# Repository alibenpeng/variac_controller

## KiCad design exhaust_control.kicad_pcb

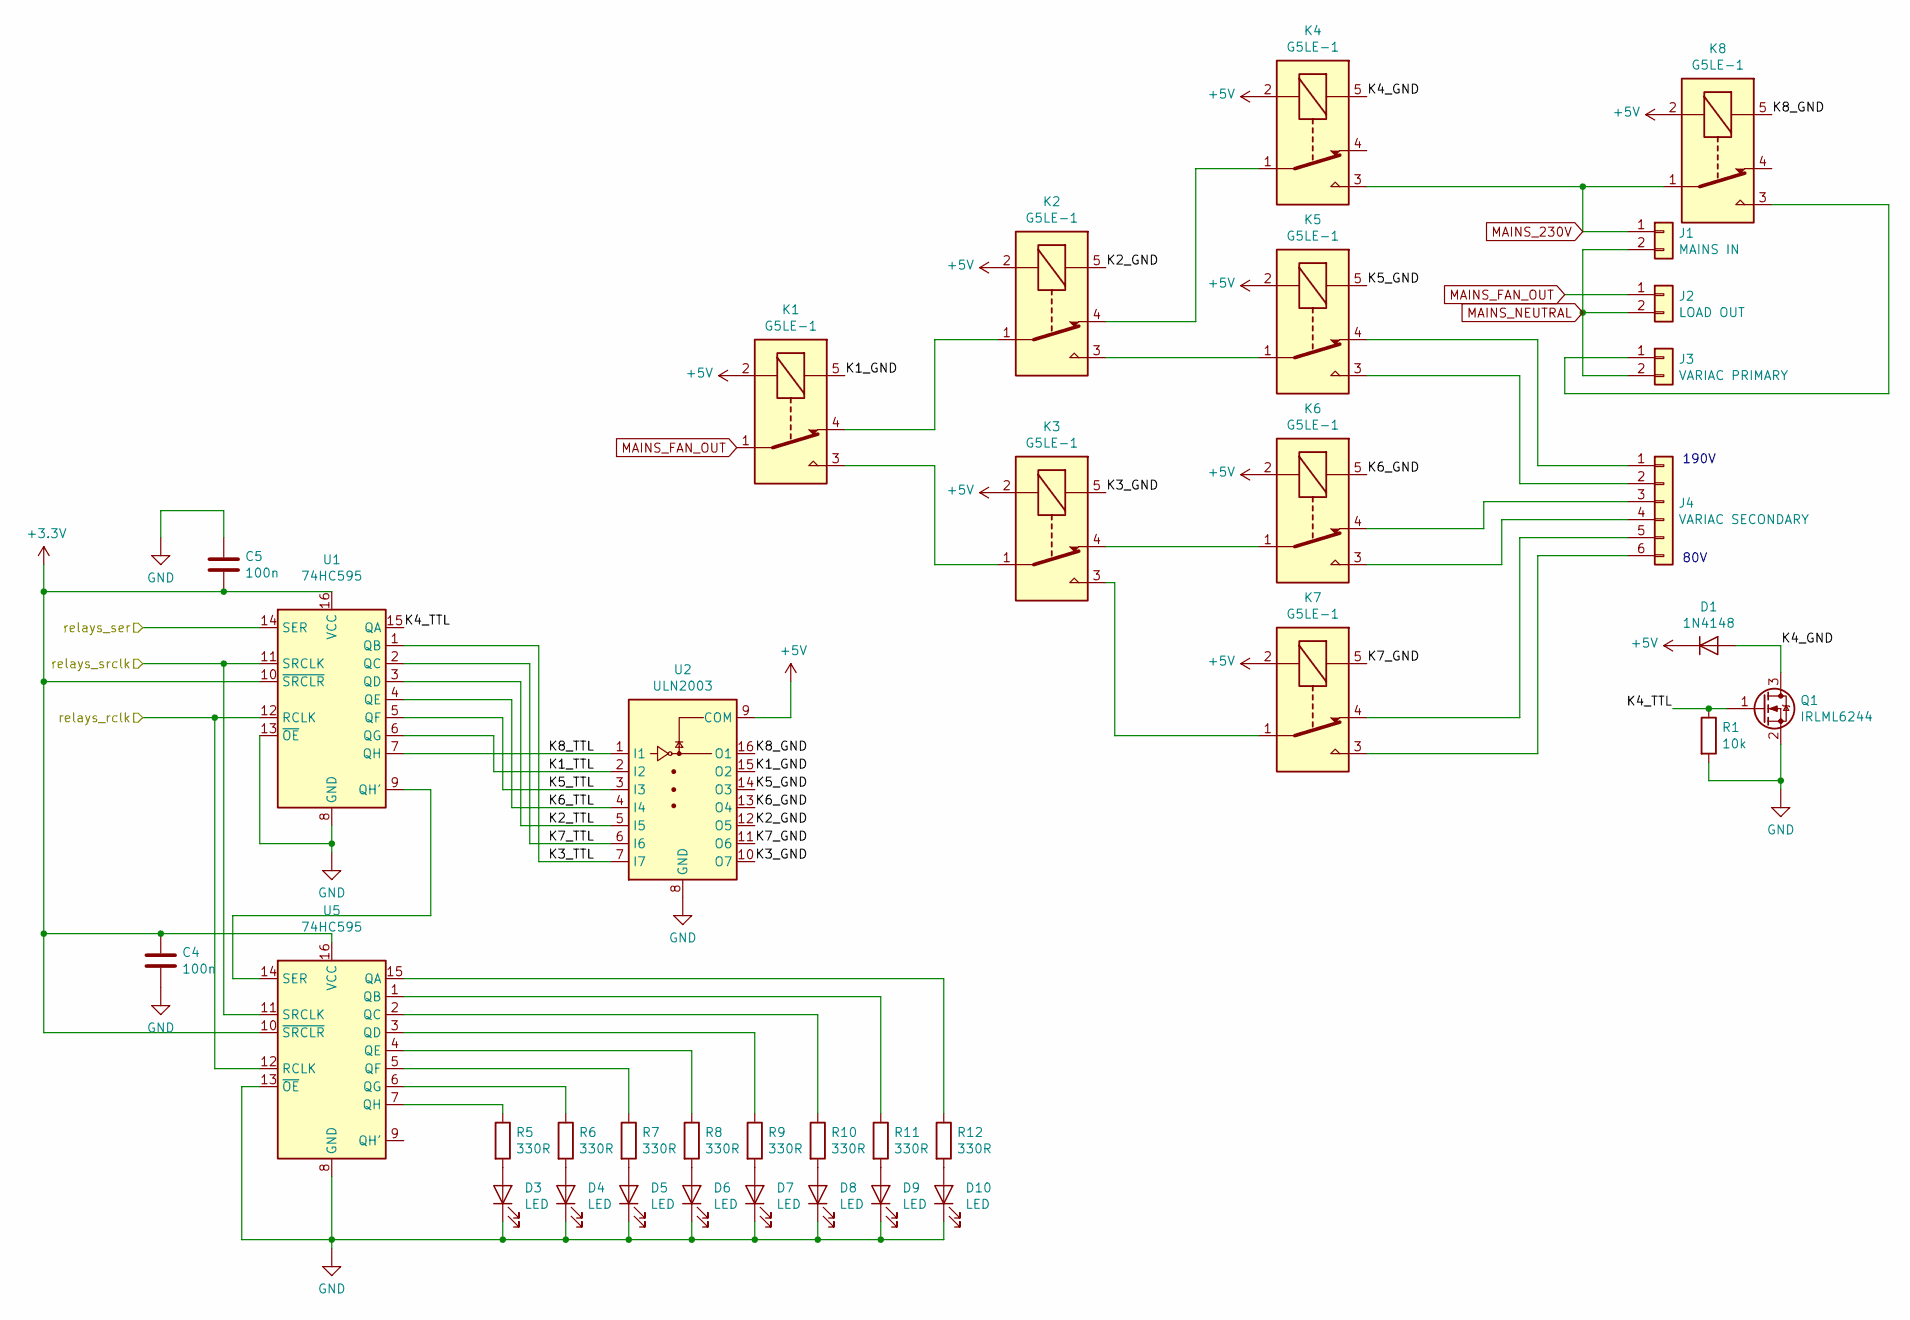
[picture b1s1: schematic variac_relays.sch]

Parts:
C4, C5: 100n; C_0402
D1: 1N4148; D_SOD-323
D3, D4, D5, D6, D7, D8, D9, D10: LED; LED-0603
J1: MAINS IN; TerminalBlock_bornier-2_P5.08mm
J2: LOAD OUT; TerminalBlock_bornier-2_P5.08mm
J3: VARIAC PRIMARY; TerminalBlock_bornier-2_P5.08mm
J4: VARIAC SECONDARY; TerminalBlock_bornier-6_P5.08mm
K1, K2, K3, K4, K5, K6, K7, K8: G5LE-1; Relay_SPDT_OMRON-G5LE-1
Q1: IRLML6244; SOT-23
R1: 10k; R_0603
R5, R6, R7, R8, R9, R10, R11, R12: 330R; R_0603
U1, U5: 74HC595; SOIC-16_3.9x9.9mm_Pitch1.27mm
U2: ULN2003; SOIC-16_3.9x9.9mm_Pitch1.27mm

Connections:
+5V: D1.1 (K), K1.2, K2.2, K3.2, K4.2, K5.2, K6.2, K7.2, K8.2, U2.9 (COM); also elsewhere on the board
/Autotransformer Relays/K1_GND: K1.5, U2.15 (O2)
/Autotransformer Relays/K1_TTL: U1.6 (QG), U2.2 (I2)
/Autotransformer Relays/K2_GND: K2.5, U2.12 (O5)
/Autotransformer Relays/K2_TTL: U1.3 (QD), U2.5 (I5)
/Autotransformer Relays/K3_GND: K3.5, U2.10 (O7)
/Autotransformer Relays/K3_TTL: U1.1 (QB), U2.7 (I7)
/Autotransformer Relays/K4_GND: D1.2 (A), K4.5, Q1.3 (D)
/Autotransformer Relays/K4_TTL: Q1.1 (G), R1.1, U1.15 (QA)
/Autotransformer Relays/K5_GND: K5.5, U2.14 (O3)
/Autotransformer Relays/K5_TTL: U1.5 (QF), U2.3 (I3)
/Autotransformer Relays/K6_GND: K6.5, U2.13 (O4)
/Autotransformer Relays/K6_TTL: U1.4 (QE), U2.4 (I4)
/Autotransformer Relays/K7_GND: K7.5, U2.11 (O6)
/Autotransformer Relays/K7_TTL: U1.2 (QC), U2.6 (I6)
/Autotransformer Relays/K8_GND: K8.5, U2.16 (O1)
/Autotransformer Relays/K8_TTL: U1.7 (QH), U2.1 (I1)
/ESP-12E/ESP_GPIO12: U1.12 (RCLK), U5.12 (RCLK); also elsewhere on the board
/ESP-12E/ESP_GPIO13: U1.14 (SER); also elsewhere on the board
/ESP-12E/ESP_GPIO16: U1.11 (SRCLK), U5.11 (SRCLK); also elsewhere on the board
GND: C4.2, C5.1, D3.1 (K), D4.1 (K), D5.1 (K), D6.1 (K), D7.1 (K), D8.1 (K), D9.1 (K), D10.1 (K), Q1.2 (S), R1.2, U1.8 (GND), U1.13 (~OE), U2.8 (GND), U5.8 (GND), U5.13 (~OE); also elsewhere on the board
MAINS_230V: J1.1, K4.3, K8.1
MAINS_FAN_OUT: J2.1, K1.1
MAINS_NEUTRAL: J1.2, J2.2, J3.2
unnamed: D3.2 (A), R5.2
unnamed: D4.2 (A), R6.2
unnamed: D5.2 (A), R7.2
unnamed: D6.2 (A), R8.2
unnamed: D7.2 (A), R9.2
unnamed: D8.2 (A), R10.2
unnamed: D9.2 (A), R11.2
unnamed: D10.2 (A), R12.2
unnamed: J3.1, K8.3
unnamed: J4.1, K5.4
unnamed: J4.2, K5.3
unnamed: J4.3, K6.4
unnamed: J4.4, K6.3
unnamed: J4.5, K7.4
unnamed: J4.6, K7.3
unnamed: K1.3, K3.1
unnamed: K1.4, K2.1
unnamed: K2.3, K5.1
unnamed: K2.4, K4.1
unnamed: K3.3, K7.1
unnamed: K3.4, K6.1
unnamed: R5.1, U5.7 (QH)
unnamed: R6.1, U5.6 (QG)
unnamed: R7.1, U5.5 (QF)
unnamed: R8.1, U5.4 (QE)
unnamed: R9.1, U5.3 (QD)
unnamed: R10.1, U5.2 (QC)
unnamed: R11.1, U5.1 (QB)
unnamed: R12.1, U5.15 (QA)
unnamed: U1.9 (QH'), U5.14 (SER)

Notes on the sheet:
80V
190V

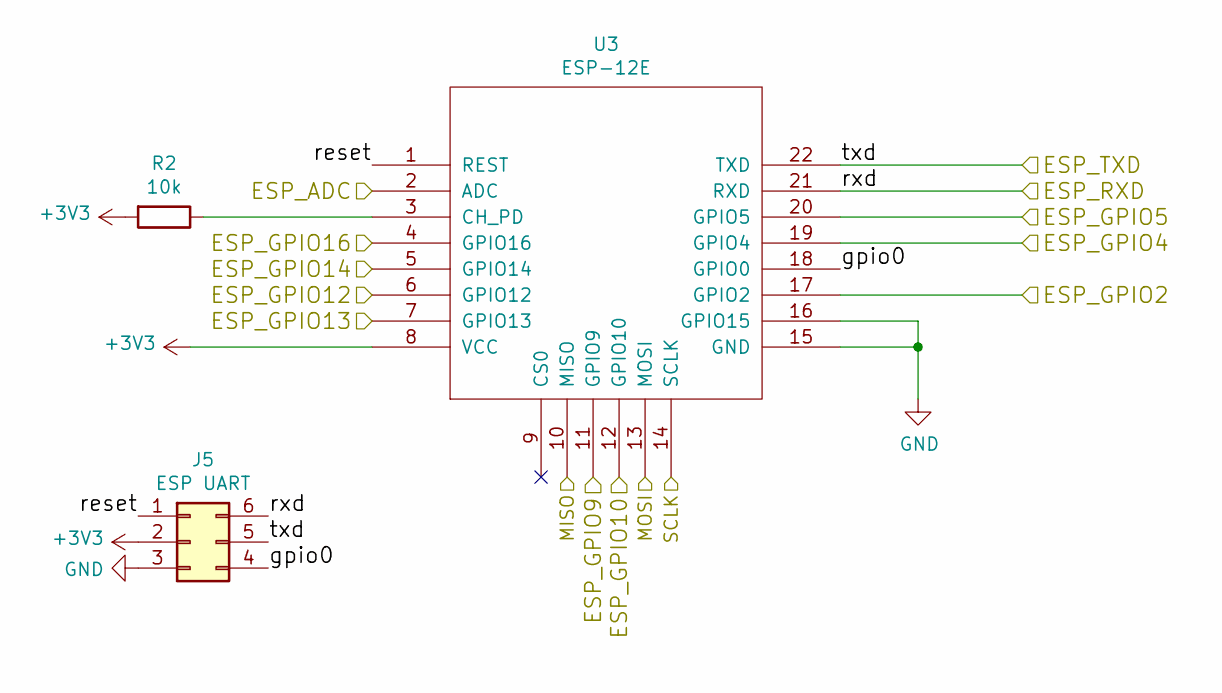
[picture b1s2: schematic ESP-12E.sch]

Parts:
J5: ESP UART; Pin_Header_Straight_2x03_Pitch2.54mm
R2: 10k; R_0603
U3: ESP-12E

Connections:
/ESP-12E/ESP_GPIO2: U3.17 (GPIO2); also elsewhere on the board
/ESP-12E/ESP_GPIO4: U3.19 (GPIO4); also elsewhere on the board
/ESP-12E/ESP_GPIO5: U3.20 (GPIO5); also elsewhere on the board
/ESP-12E/ESP_GPIO9: U3.11 (GPIO9); also elsewhere on the board
/ESP-12E/ESP_GPIO10: U3.12 (GPIO10); also elsewhere on the board
/ESP-12E/ESP_GPIO12: U3.6 (GPIO12); also elsewhere on the board
/ESP-12E/ESP_GPIO13: U3.7 (GPIO13); also elsewhere on the board
/ESP-12E/ESP_GPIO14: U3.5 (GPIO14); also elsewhere on the board
/ESP-12E/ESP_GPIO16: U3.4 (GPIO16); also elsewhere on the board
/ESP-12E/ESP_RXD: J5.6, U3.21 (RXD)
/ESP-12E/ESP_TXD: J5.5, U3.22 (TXD)
/ESP-12E/MISO: U3.10 (MISO); also elsewhere on the board
/ESP-12E/MOSI: U3.13 (MOSI); also elsewhere on the board
/ESP-12E/SCLK: U3.14 (SCLK); also elsewhere on the board
/ESP-12E/gpio0: J5.4, U3.18 (GPIO0)
/ESP-12E/reset: J5.1, U3.1 (REST)
/I/O/ADC: U3.2 (ADC); also elsewhere on the board
GND: J5.3, U3.15 (GND), U3.16 (GPIO15); also elsewhere on the board
unnamed: R2.1, U3.3 (CH_PD)

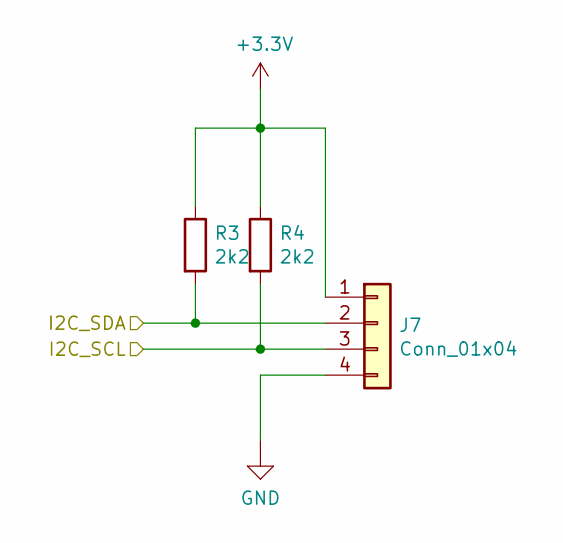
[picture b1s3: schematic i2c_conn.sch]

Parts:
J7: Conn_01x04; Pin_Header_Angled_1x04_Pitch2.54mm
R3, R4: 2k2; R_0603

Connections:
/ESP-12E/ESP_GPIO2: J7.2, R3.2; also elsewhere on the board
/ESP-12E/ESP_GPIO14: J7.3, R4.2; also elsewhere on the board
GND: J7.4; also elsewhere on the board

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
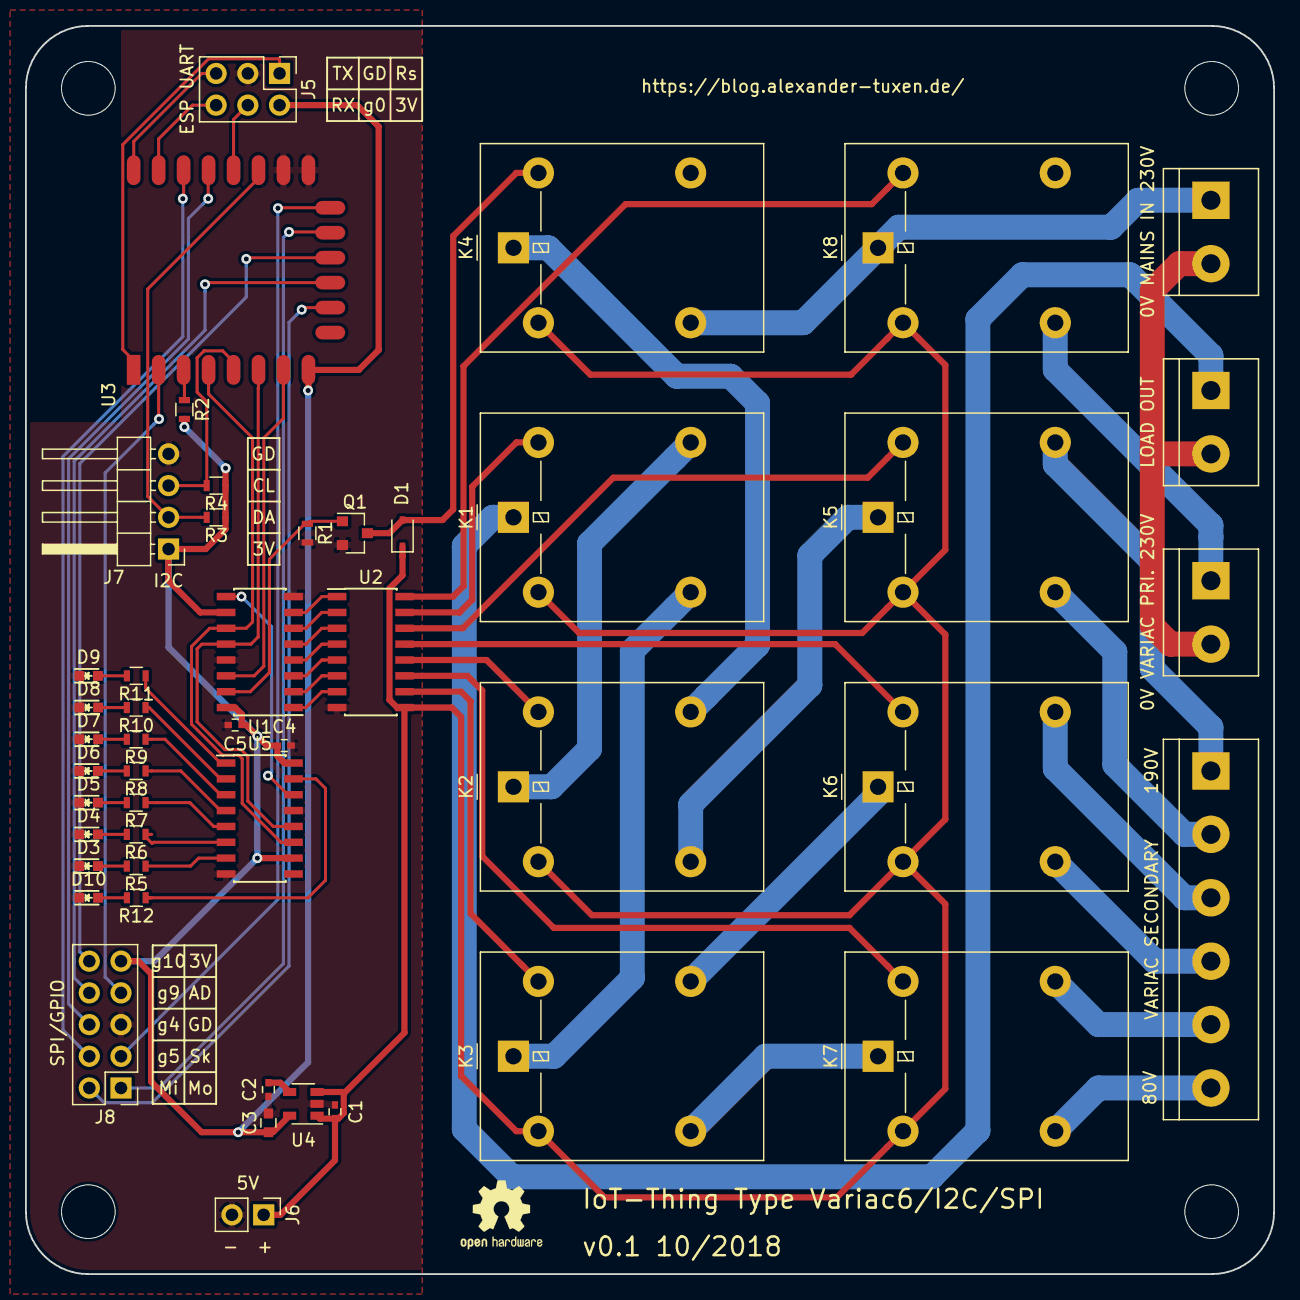
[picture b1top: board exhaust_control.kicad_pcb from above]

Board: 2 copper layers, 100.0 x 100.0 mm, 52 parts (0 on the bottom side), 71 nets.

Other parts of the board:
C1: 1u; C_0402
C2: 10n; C_0402
C3: 2.2u; C_0603
J6: Conn_01x02; Pin_Header_Straight_1x02_Pitch2.54mm
J8: Conn_02x05_Odd_Even; Pin_Header_Straight_2x05_Pitch2.54mm
MH1, MH2, MH3, MH4: MountingHole; MountingHole_4.3mm_M4
U4: LP2985LV; SOT-23-5

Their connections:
+5V: C1.1, J6.1, U4.1, U4.3; also elsewhere on the board
/ESP-12E/ESP_GPIO4: J8.6; also elsewhere on the board
/ESP-12E/ESP_GPIO5: J8.4; also elsewhere on the board
/ESP-12E/ESP_GPIO9: J8.8; also elsewhere on the board
/ESP-12E/ESP_GPIO10: J8.10; also elsewhere on the board
/ESP-12E/MISO: J8.2; also elsewhere on the board
/ESP-12E/MOSI: J8.1; also elsewhere on the board
/ESP-12E/SCLK: J8.3; also elsewhere on the board
/I/O/ADC: J8.7; also elsewhere on the board
GND: C1.2, C2.2, C3.2, J6.2, J8.5, U4.2; also elsewhere on the board
unnamed: C2.1, U4.4
